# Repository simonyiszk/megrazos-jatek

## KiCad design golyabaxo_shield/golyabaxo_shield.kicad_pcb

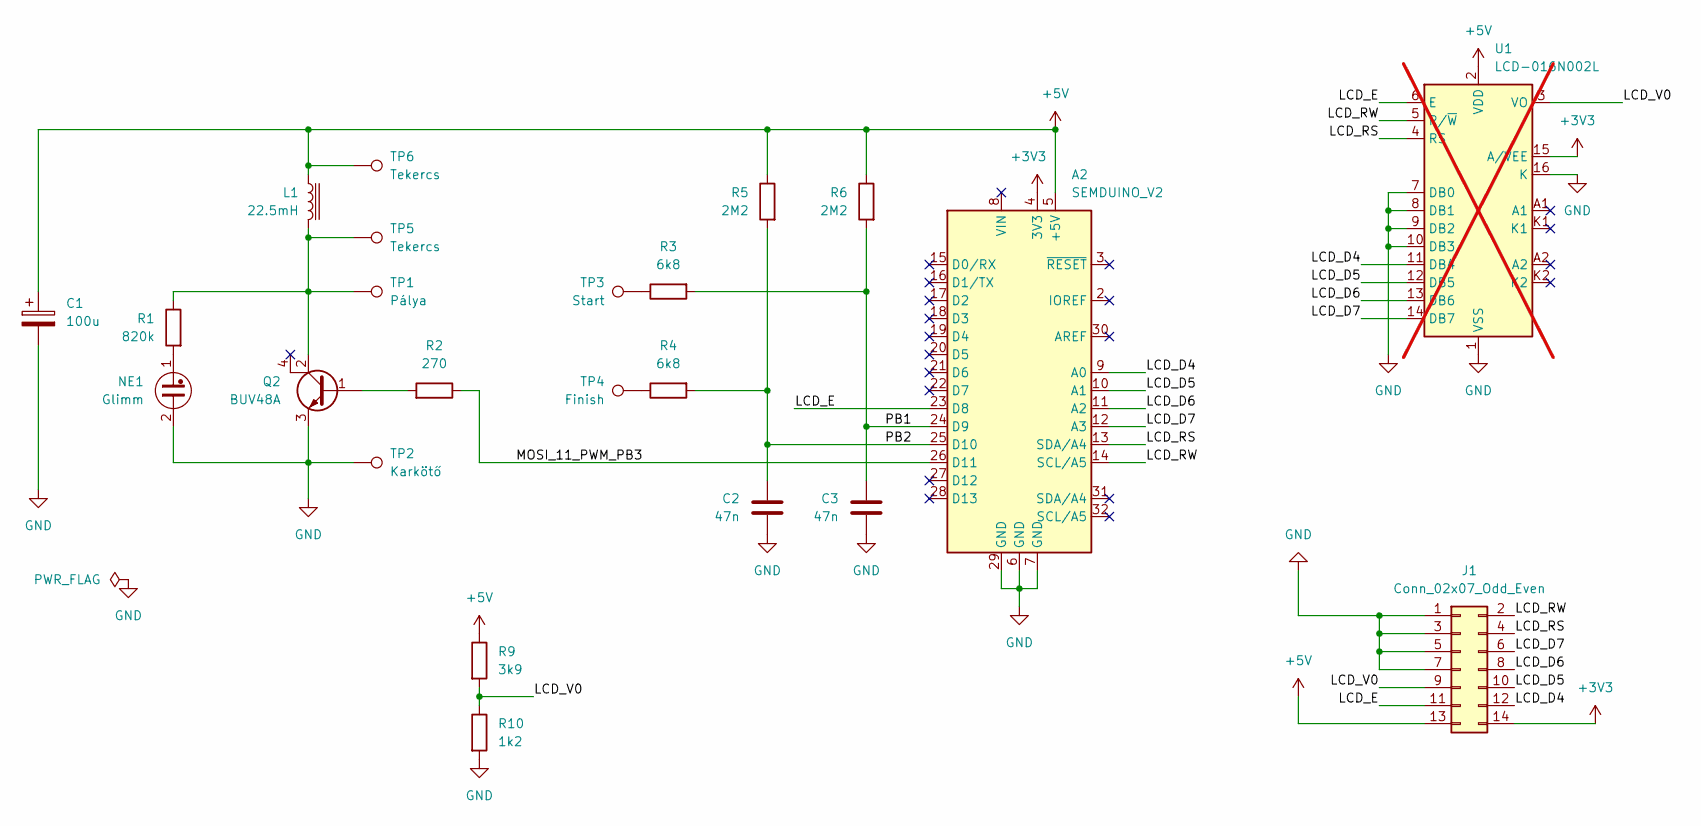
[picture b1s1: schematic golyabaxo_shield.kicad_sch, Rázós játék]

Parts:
A2: SEMDUINO_V2; Arduino_UNO_R3
C1: 100u; CP_Radial_D7.5mm_P2.50mm
C2, C3: 47n; C_Disc_D3.8mm_W2.6mm_P2.50mm
J1: Conn_02x07_Odd_Even; PinHeader_2x07_P2.54mm_Vertical_SMD
L1: 22.5mH
NE1: Glimm; LED_D5.0mm_IRGrey
Q2: BUV48A; TO-218-3_Horizontal_TabDown
R1: 820k; R_Axial_DIN0207_L6.3mm_D2.5mm_P10.16mm_Horizontal
R2: 270; R_Axial_DIN0207_L6.3mm_D2.5mm_P10.16mm_Horizontal
R3, R4: 6k8; R_Axial_DIN0207_L6.3mm_D2.5mm_P10.16mm_Horizontal
R5, R6: 2M2; R_Axial_DIN0207_L6.3mm_D2.5mm_P10.16mm_Horizontal
R9: 3k9; R_Axial_DIN0207_L6.3mm_D2.5mm_P10.16mm_Horizontal
R10: 1k2; R_Axial_DIN0207_L6.3mm_D2.5mm_P10.16mm_Horizontal
TP1: Pálya; TestPoint_Pad_D2.5mm
TP2: Karkötő; TestPoint_Pad_D2.5mm
TP3: Start; TestPoint_Pad_D2.5mm
TP4: Finish; TestPoint_Pad_D2.5mm
TP5, TP6: Tekercs; TestPoint_Pad_D2.5mm
U1: LCD-016N002L; not fitted

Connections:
+3V3: A2.4 (3V3), J1.14, U1.15 (A/VEE)
+5V: A2.5 (+5V), C1.1, J1.13, L1.2, R5.1, R6.1, R9.1, TP6.1, U1.2 (VDD)
/LCD_D4: A2.9 (A0), J1.12, U1.11 (DB4)
/LCD_D5: A2.10 (A1), J1.10, U1.12 (DB5)
/LCD_D6: A2.11 (A2), J1.8, U1.13 (DB6)
/LCD_D7: A2.12 (A3), J1.6, U1.14 (DB7)
/LCD_E: A2.23 (D8), J1.11, U1.6 (E)
/LCD_RS: A2.13 (SDA/A4), J1.4, U1.4 (RS)
/LCD_RW: A2.14 (SCL/A5), J1.2, U1.5 (R/~W)
/LCD_V0: J1.9, R9.2, R10.1, U1.3 (VO)
/MOSI_11_PWM_PB3: A2.26 (D11), R2.1
/PB1: A2.24 (D9), C3.1, R3.2, R6.2
/PB2: A2.25 (D10), C2.1, R4.2, R5.2
GND: A2.6 (GND), A2.7 (GND), A2.29 (GND), C1.2, C2.2, C3.2, J1.1, J1.3, J1.5, J1.7, NE1.2, Q2.3 (E), R10.2, TP2.1, U1.1 (VSS), U1.7 (DB0), U1.8 (DB1), U1.9 (DB2), U1.10 (DB3), U1.16 (K)
unnamed: NE1.1, R1.2
unnamed: Q2.1 (B), R2.2
unnamed: L1.1, Q2.2 (C), R1.1, TP1.1, TP5.1
unnamed: R3.1, TP3.1
unnamed: R4.1, TP4.1

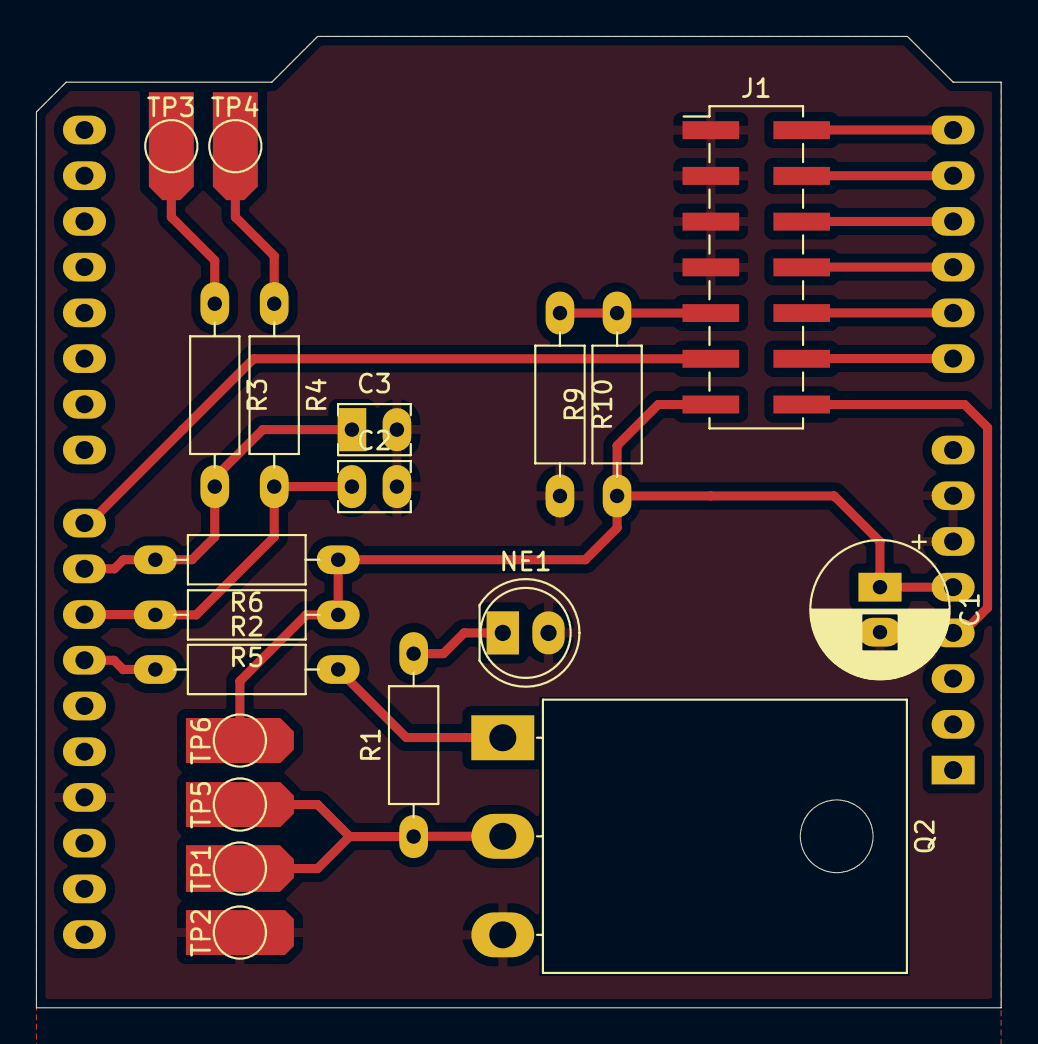
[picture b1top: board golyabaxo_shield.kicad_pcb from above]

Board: 2 copper layers, 53.6 x 54.0 mm, 21 parts (1 on the bottom side), 19 nets.

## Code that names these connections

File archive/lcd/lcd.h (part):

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#define LCD_DATA3_PIN    3            /**< pin for 4bit data bit 3  */
#endif
#ifndef LCD_RS_PORT
#define LCD_RS_PORT      LCD_PORT     /**< port for RS line         */
#endif
#ifndef LCD_RS_PIN
#define LCD_RS_PIN       4            /**< pin  for RS line         */
#endif
#ifndef LCD_RW_PORT
#define LCD_RW_PORT      LCD_PORT     /**< port for RW line         */
#endif
#ifndef LCD_RW_PIN
#define LCD_RW_PIN       5            /**< pin  for RW line         */
#endif
#ifndef LCD_E_PORT
#define LCD_E_PORT       PORTB     /**< port for Enable line     */
#endif
#ifndef LCD_E_PIN
#define LCD_E_PIN        0            /**< pin  for Enable line     */
#endif

#elif defined(__AVR_AT90S4414__) || defined(__AVR_AT90S8515__) || defined(__AVR_ATmega64__) || \
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
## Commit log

2024-03-18 Original project files from Important
2024-04-21 Add SEMduino shield compatible with the current wiring
2024-04-21 Add refurbished firmware for SEMduino-V2 - testing needed
2024-04-24 Build SEMduino shield
2024-04-24 Magyar nyelvű a firmware

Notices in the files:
archive/lcd/lcd.h:
@copyright (C) 2015 Peter Fleury, GNU General Public License Version 3
